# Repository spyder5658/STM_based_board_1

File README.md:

# STM32-Based Board Project
This repository contains the design files for an STM32-based custom board. The project includes KiCad files for the schematic and PCB layout, as well as a 3D model (.stp) of the board. The design is tailored for embedded system applications, making use of the STM32 microcontroller for a range of development purposes.

## Features
- STM32 MCU-based design
- KiCad project files for easy customization
- 3D model for visualization
## Usage
- Open the KiCad files to view and modify the design.
- Use the provided 3D model for visualizing or planning enclosures.
Preview

License
This project is licensed under the MIT License.

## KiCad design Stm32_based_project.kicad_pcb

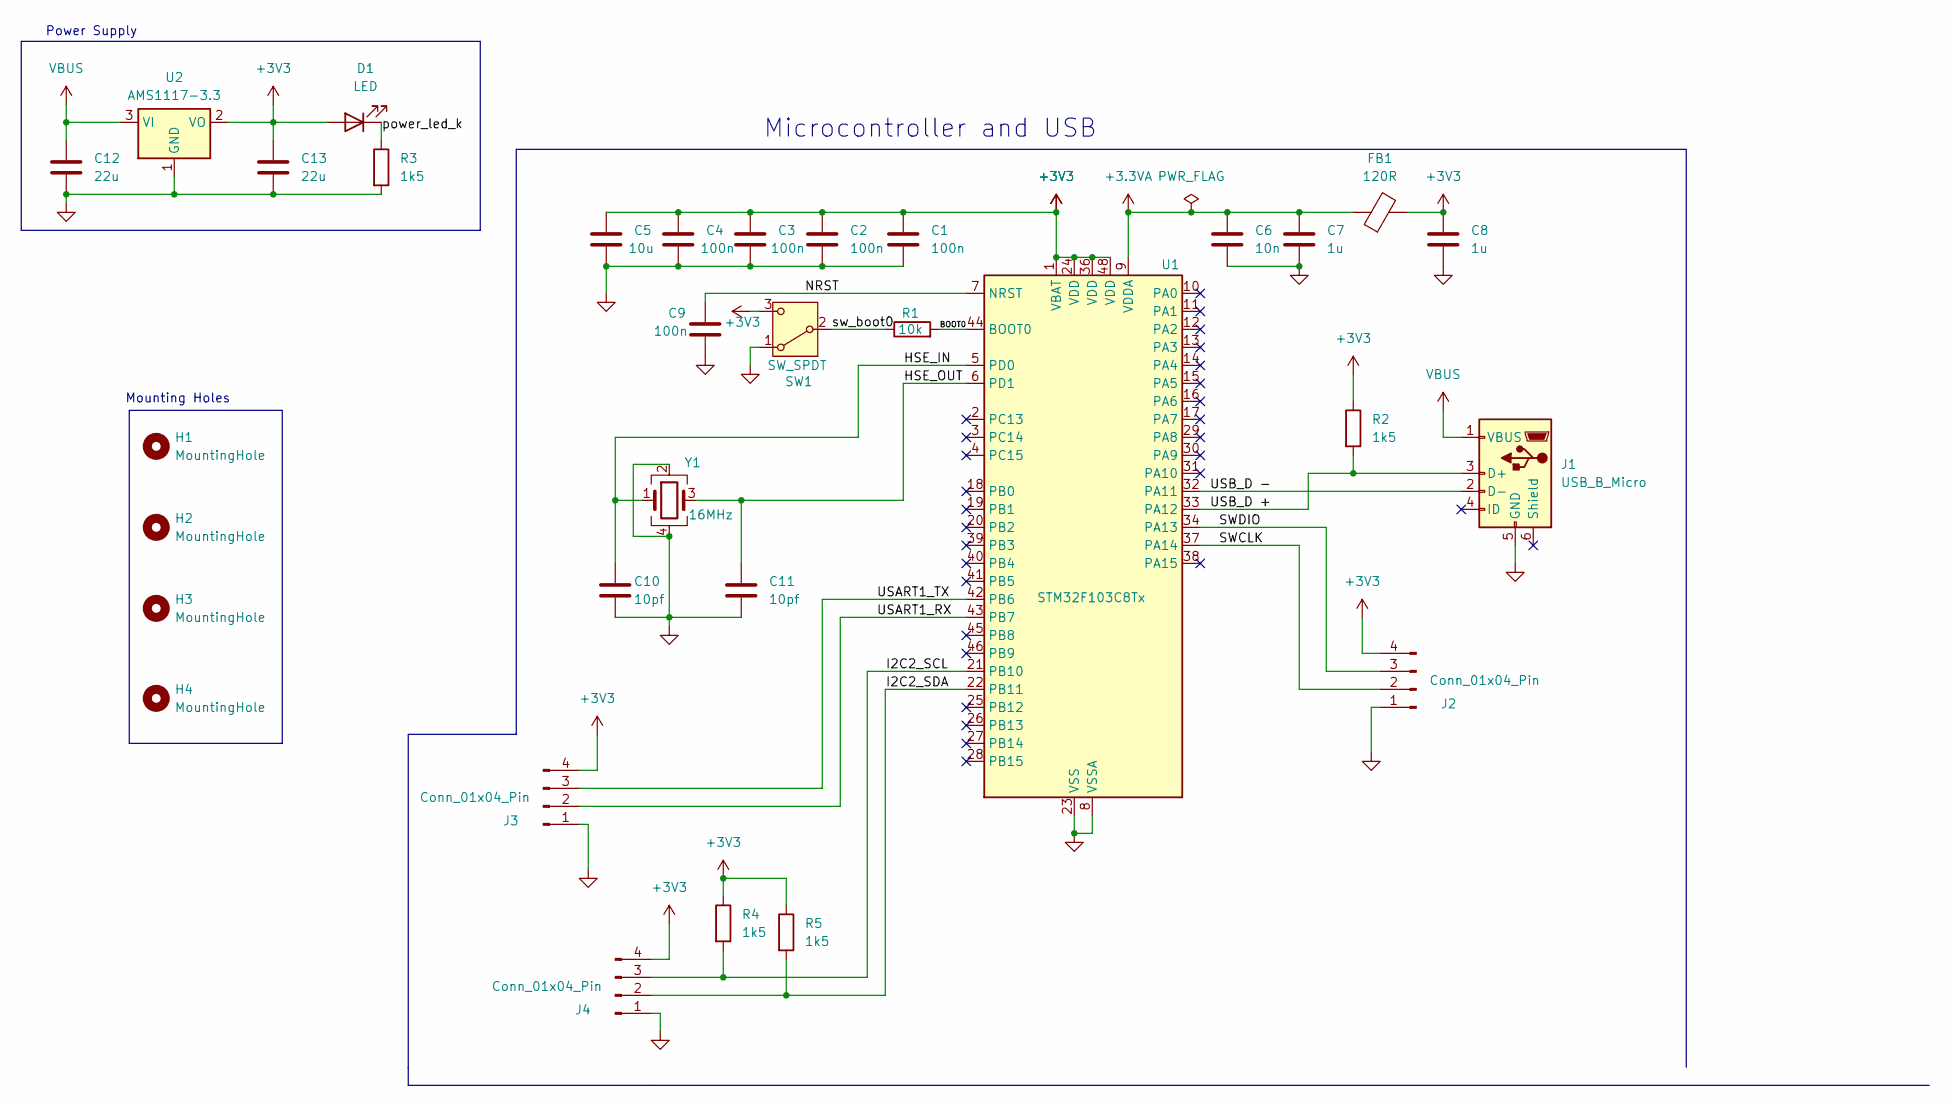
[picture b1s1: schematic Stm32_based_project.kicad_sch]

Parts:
C1, C2, C3, C4, C9: 100n; C_0402_1005Metric
C5: 10u; C_0603_1608Metric
C6: 10n; C_0402_1005Metric
C7, C8: 1u; C_0402_1005Metric
C10, C11: 10pf; C_0402_1005Metric
C12, C13: 22u; C_0805_2012Metric
D1: LED; LED_0402_1005Metric
FB1: 120R; L_0603_1608Metric
H1, H2, H3, H4: MountingHole; MountingHole_2.2mm_M2
J1: USB_B_Micro; USB_Micro-B_Wuerth_629105150521
J2, J3, J4: Conn_01x04_Pin; PinHeader_1x04_P2.54mm_Vertical
R1: 10k; R_0402_1005Metric
R2, R3, R4, R5: 1k5; R_0402_1005Metric
SW1: SW_SPDT; SW_SPDT_PCM12
U1: STM32F103C8Tx; LQFP-48_7x7mm_P0.5mm
U2: AMS1117-3.3; SOT-223-3_TabPin2
Y1: 16MHz; Crystal_SMD_3225-4Pin_3.2x2.5mm

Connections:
+3.3VA: C6.1, C7.1, FB1.1, U1.9 (VDDA)
+3V3: C1.1, C2.1, C3.1, C4.1, C5.1, C8.1, C13.1, D1.2 (A), FB1.2, J2.4, J3.4, J4.4, R2.1, R4.1, R5.1, SW1.3 (C), U1.1 (VBAT), U1.24 (VDD), U1.36 (VDD), U1.48 (VDD), U2.2 (VO)
/BOOT0: R1.2, U1.44 (BOOT0)
/HSE_IN: C10.1, U1.5 (PD0), Y1.1
/HSE_OUT: C11.1, U1.6 (PD1), Y1.3
/I2C2_SCL: J4.3, R4.2, U1.21 (PB10)
/I2C2_SDA: J4.2, R5.2, U1.22 (PB11)
/NRST: C9.1, U1.7 (NRST)
/SWCLK: J2.2, U1.37 (PA14)
/SWDIO: J2.3, U1.34 (PA13)
/USART1_RX: J3.2, U1.43 (PB7)
/USART1_TX: J3.3, U1.42 (PB6)
/USB_D +: J1.3 (D+), R2.2, U1.33 (PA12)
/USB_D -: J1.2 (D-), U1.32 (PA11)
/power_led_k: D1.1 (K), R3.1
/sw_boot0: R1.1, SW1.2 (B)
GND: C1.2, C2.2, C3.2, C4.2, C5.2, C6.2, C7.2, C8.2, C9.2, C10.2, C11.2, C12.2, C13.2, J1.5 (GND), J2.1, J3.1, J4.1, R3.2, SW1.1 (A), U1.8 (VSSA), U1.23 (VSS), U1.35 (VSS), U1.47 (VSS), U2.1 (GND), Y1.2, Y1.4
VBUS: C12.1, J1.1 (VBUS), U2.3 (VI)

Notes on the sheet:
Mounting Holes
Microcontroller and USB
Power Supply

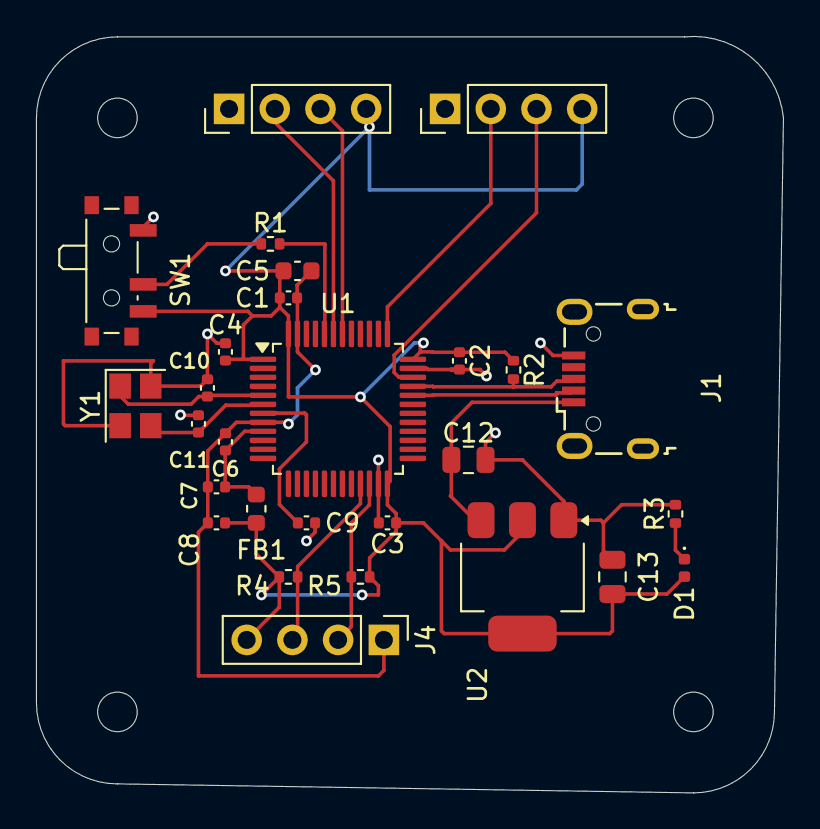
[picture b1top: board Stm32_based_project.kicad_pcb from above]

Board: 2 copper layers, 41.5 x 42.0 mm, 32 parts (0 on the bottom side), 18 nets.

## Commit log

2024-10-13 stm based board kicad files
